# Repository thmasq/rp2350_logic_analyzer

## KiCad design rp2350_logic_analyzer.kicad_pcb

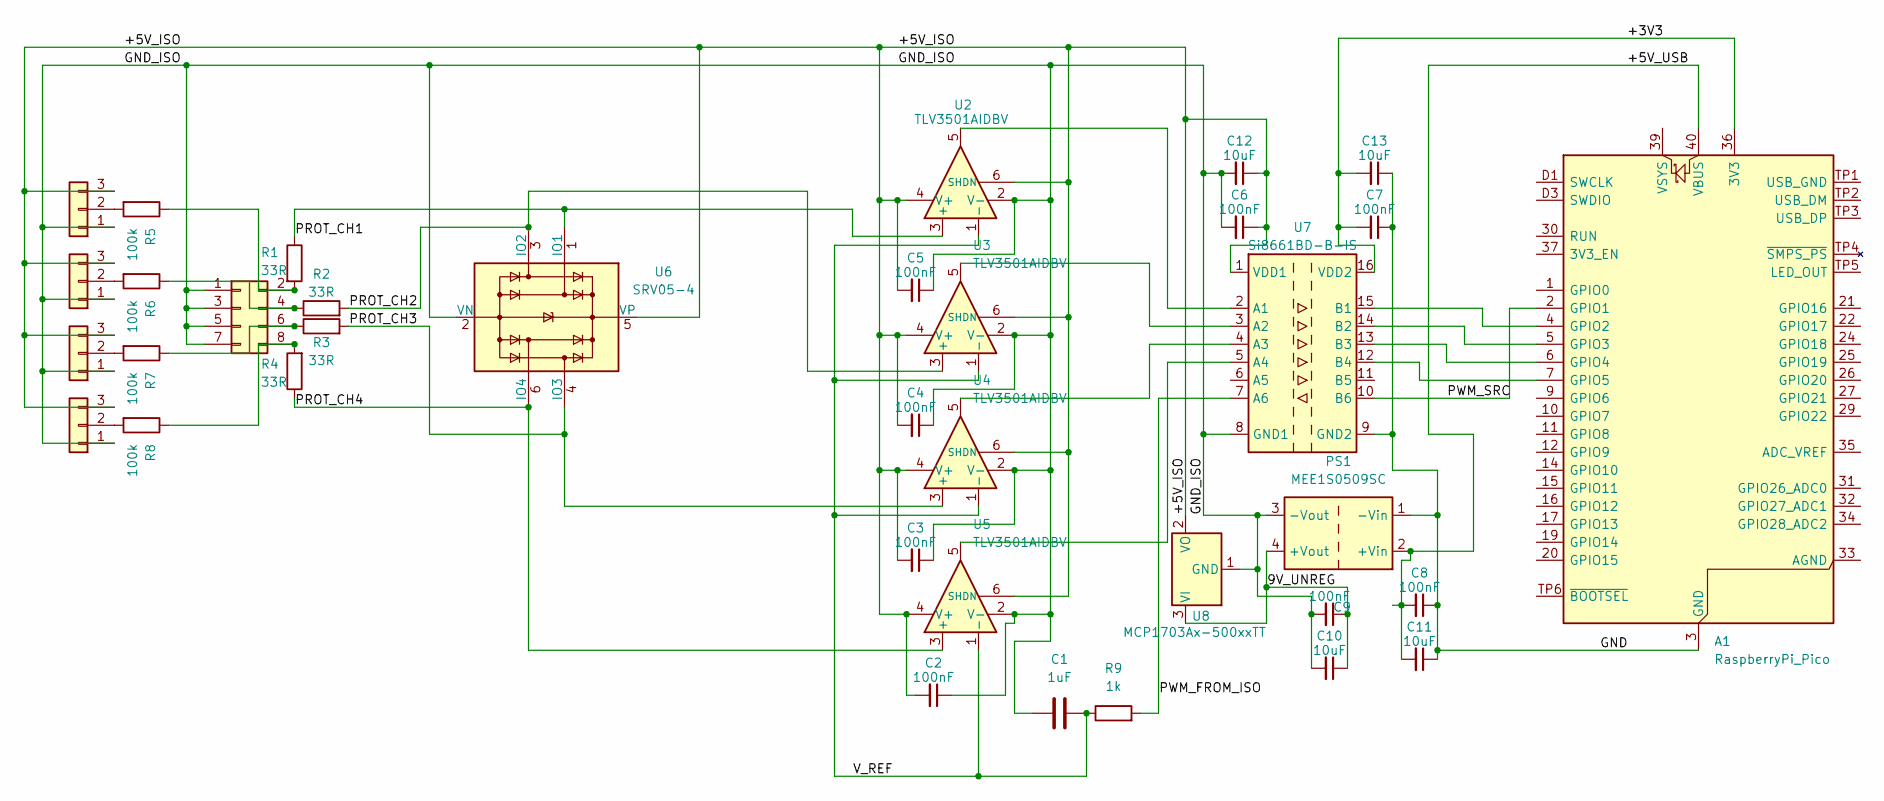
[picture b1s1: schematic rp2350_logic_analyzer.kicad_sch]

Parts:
A1: RaspberryPi_Pico; RaspberryPi_Pico_SMD
C1: 1uF; C_0603_1608Metric
C2, C3, C4, C5, C6, C7, C8, C9: 100nF; C_0603_1608Metric
C10, C11, C12, C13: 10uF; C_0805_2012Metric
J1: Conn_02x04; PinHeader_2x04_P2.54mm_Vertical
J2, J3, J4, J5: Conn_01x03; PinHeader_1x03_P2.54mm_Vertical
PS1: MEE1S0509SC; Converter_DCDC_Murata_MEE1SxxxxSC_THT
R1, R2, R3, R4: 33R; R_0603_1608Metric
R5, R6, R7, R8: 100k; R_0603_1608Metric
R9: 1k; R_0603_1608Metric
U2, U3, U4, U5: TLV3501AIDBV; SOT-23-6
U6: SRV05-4; SOT-23-6
U7: Si8661BD-B-IS; SOIC-16W_7.5x10.3mm_P1.27mm
U8: MCP1703Ax-500xxTT; SOT-23

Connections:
/9V_UNREG: C9.1, C10.1, PS1.4 (+Vout), U8.3 (VI)
/+3V3: A1.36 (3V3), C7.2, C13.2, U7.16 (VDD2)
/+5V_ISO: C2.2, C3.2, C4.2, C5.2, C6.1, C12.1, J2.3, J3.3, J4.3, J5.3, U2.4 (V+), U2.6 (SHDN), U3.4 (V+), U3.6 (SHDN), U4.4 (V+), U4.6 (SHDN), U5.4 (V+), U5.6 (SHDN), U6.5 (VP), U7.1 (VDD1), U8.2 (VO)
/+5V_USB: A1.40 (VBUS), C8.2, C11.2, PS1.2 (+Vin)
/GND: A1.3 (GND), A1.8 (GND), A1.13 (GND), A1.18 (GND), A1.23 (GND), A1.28 (GND), A1.38 (GND), A1.D2 (GND), C7.1, C8.1, C11.1, C13.1, PS1.1 (-Vin), U7.9 (GND2)
/GND_ISO: C1.1, C2.1, C3.1, C4.1, C5.1, C6.2, C9.2, C10.2, C12.2, J1.1, J1.3, J1.5, J1.7, J2.1, J3.1, J4.1, J5.1, PS1.3 (-Vout), U2.2 (V-), U3.2 (V-), U4.2 (V-), U5.2 (V-), U6.2 (VN), U7.8 (GND1), U8.1 (GND)
/PROT_CH1: R1.1, U2.3 (+), U6.1 (IO1)
/PROT_CH2: R2.2, U3.3 (+), U6.3 (IO2)
/PROT_CH3: R3.2, U4.3 (+), U6.4 (IO3)
/PROT_CH4: R4.1, U5.3 (+), U6.6 (IO4)
/PWM_FROM_ISO: R9.2, U7.7 (A6)
/PWM_SRC: A1.2 (GPIO1), U7.10 (B6)
/V_REF: C1.2, R9.1, U2.1 (-), U3.1 (-), U4.1 (-), U5.1 (-)
unnamed: A1.4 (GPIO2), U7.15 (B1)
unnamed: A1.5 (GPIO3), U7.14 (B2)
unnamed: A1.6 (GPIO4), U7.13 (B3)
unnamed: A1.7 (GPIO5), U7.12 (B4)
unnamed: J1.2, R1.2, R5.1
unnamed: J1.4, R2.1, R6.1
unnamed: J1.6, R3.1, R7.1
unnamed: J1.8, R4.2, R8.1
unnamed: J2.2, R5.2
unnamed: J3.2, R6.2
unnamed: J4.2, R7.2
unnamed: J5.2, R8.2
unnamed: U2.5, U7.2 (A1)
unnamed: U3.5, U7.3 (A2)
unnamed: U4.5, U7.4 (A3)
unnamed: U5.5, U7.5 (A4)

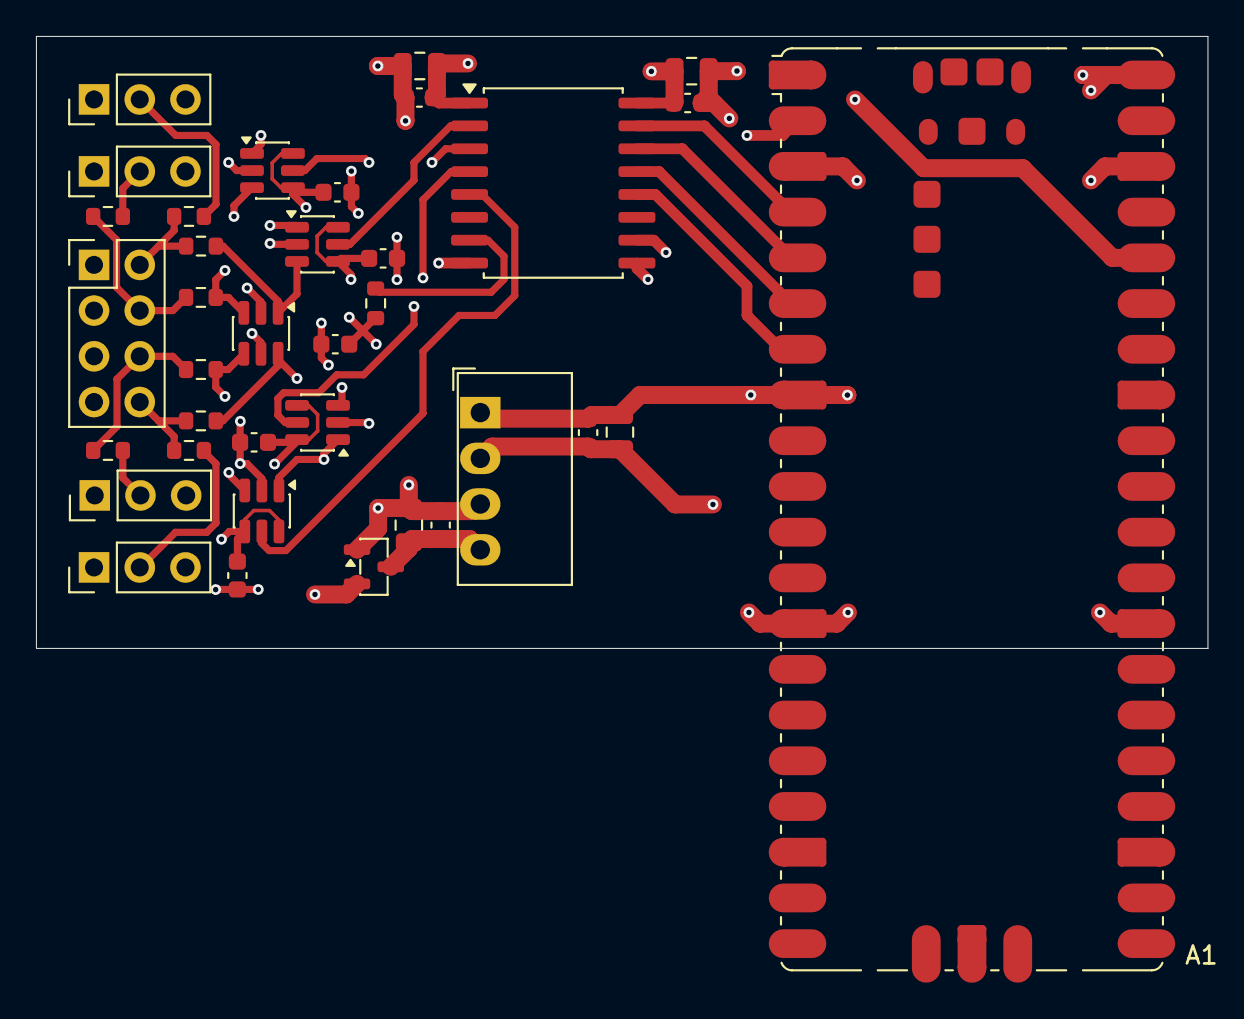
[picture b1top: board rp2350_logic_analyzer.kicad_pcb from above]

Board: 4 copper layers, 65.1 x 34.0 mm, 36 parts (0 on the bottom side), 29 nets.

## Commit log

2025-12-17 Initialize repository
2025-12-17 Replace ISO7761FDBQ with SI8661BD-B-IS
2025-12-17 Improve grounding
2025-12-17 Improve schematic organization
2025-12-18 Revamp power supply side
2025-12-18 Position newly added LDO
